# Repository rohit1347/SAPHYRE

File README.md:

# SAPHYRE
PCB for final year project.

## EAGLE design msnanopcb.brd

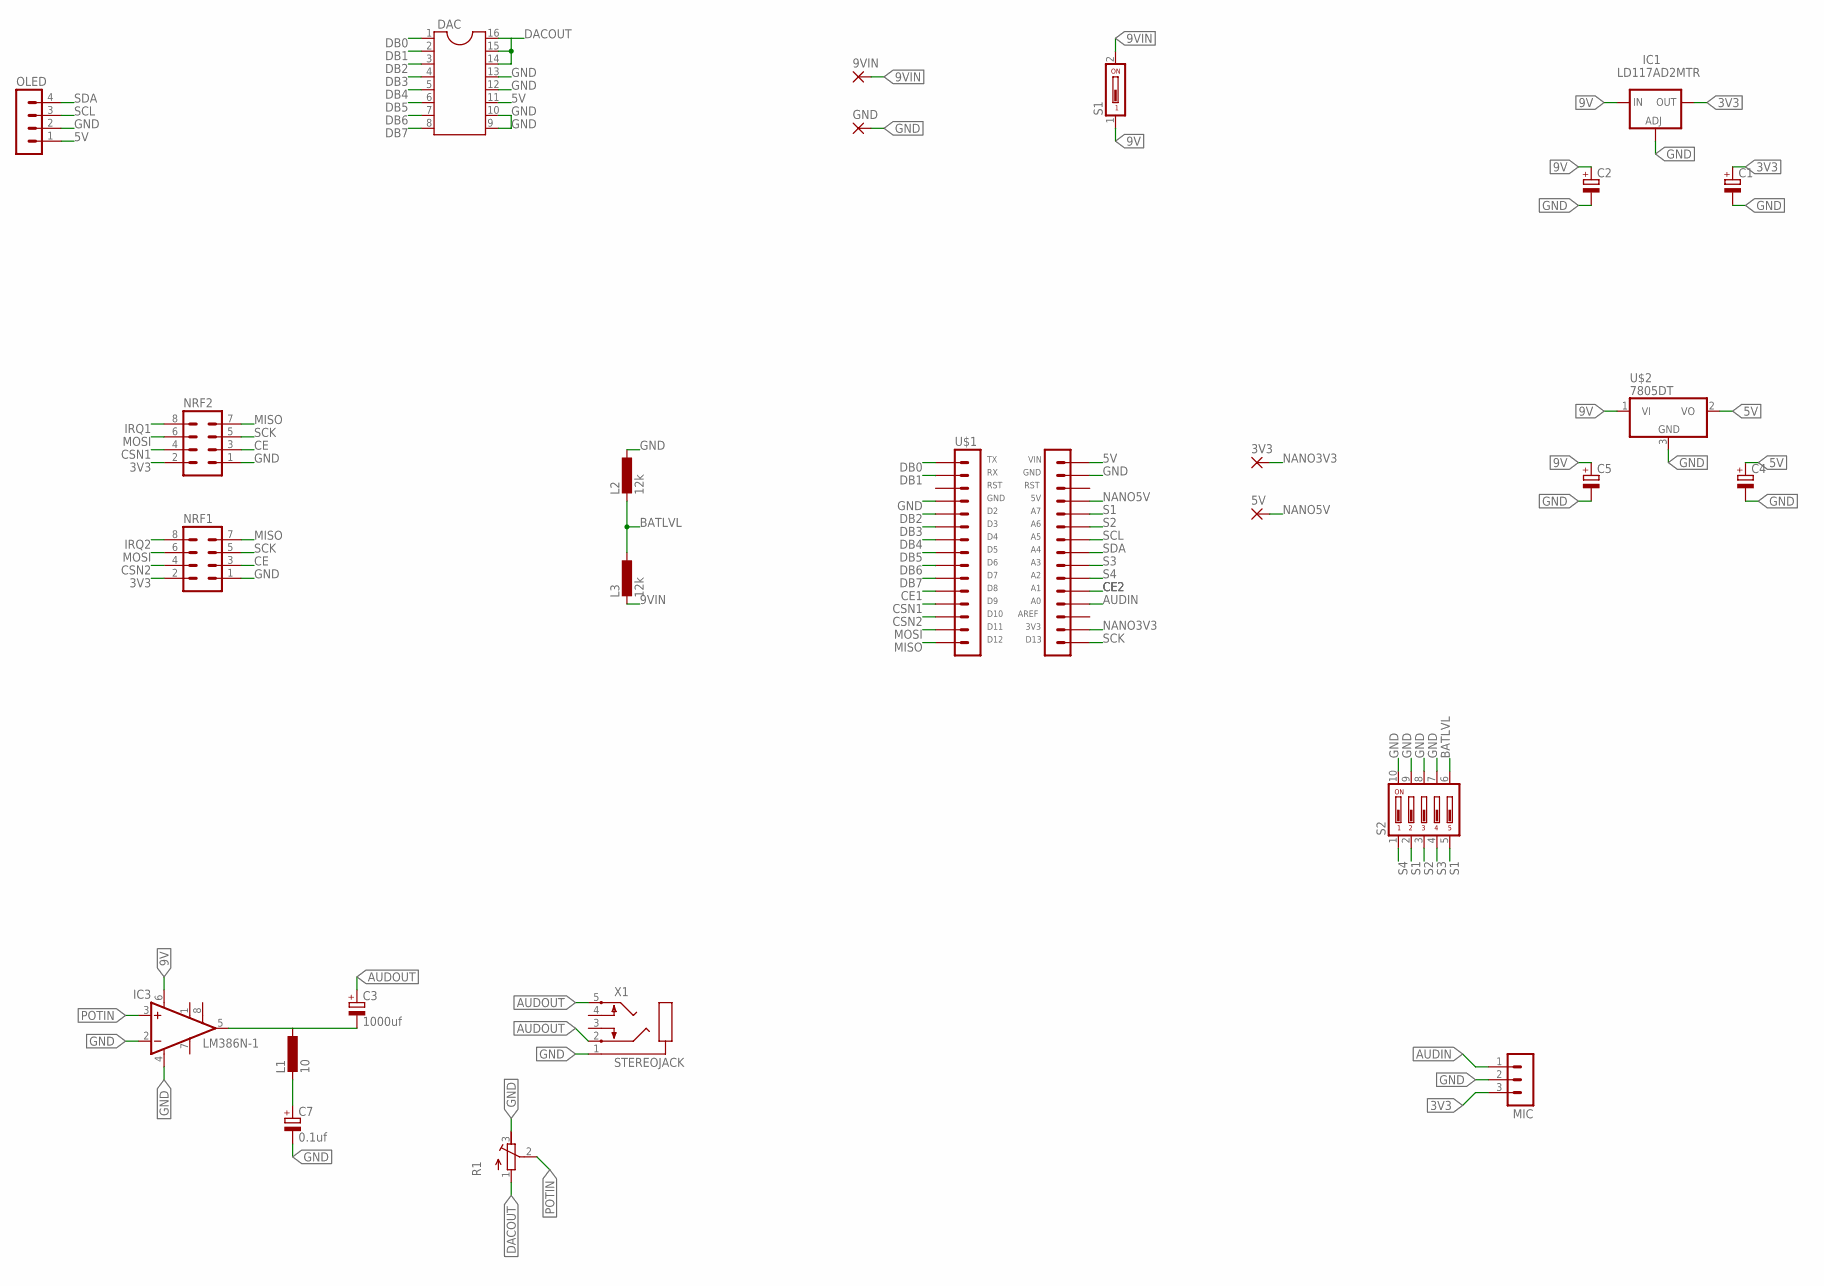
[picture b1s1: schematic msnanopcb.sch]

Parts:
3V3, 5V, 9VIN: WIREPADSMD1,27-254; SMD1,27-2,54
C1, C2, C4, C5: CPOL-EUE2,5-6E; E2,5-6E
C3: 1000uf; E3,5-8
C7: 0.1uf; E2-5
DAC: DIL16S; SOCKET-16
GND: WIREPADSMD1,27-254; SMD1,27-2,54
IC1: LD117AD2MTR; D2PACK
IC3: LM386N-1; DIL08
L1: 10; 0204/7
L2, L3: 12k; 0204/7
MIC: MA03-1
NRF1, NRF2: MA04-2
OLED: MA04-1
R1: R-TRIMM3296P; RTRIM3296P
S1: DS01; DS-01
S2: DS05; DS-05
U$1: ARD-NANO
U$2: 7805DT; TO252
X1: STEREOJACK; STX3100

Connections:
3V3: C1.+, IC1.2 (OUT), MIC.3, NRF1.2, NRF2.2
5V: C4.+, DAC.11, OLED.1, U$1.VIN, U$2.2 (VO)
9V: C2.+, C5.+, IC1.3 (IN), IC3.6 (VS), S1.1, U$2.1 (VI)
9VIN: 9VIN.1, L3.2, S1.2
AUDIN: MIC.1, U$1.A0
AUDOUT: C3.+, X1.2, X1.5
BATLVL: L2.2, L3.1, S2.6
CE: NRF1.3, NRF2.3
CE1: U$1.D8
CE2: U$1.A1
CSN1: NRF2.4, U$1.D9
CSN2: NRF1.4, U$1.D10
DACOUT: DAC.14, DAC.15, DAC.16, R1.1 (A)
DB0: DAC.1, U$1.TX
DB1: DAC.2, U$1.RX
DB2: DAC.3, U$1.D2
DB3: DAC.4, U$1.D3
DB4: DAC.5, U$1.D4
DB5: DAC.6, U$1.D5
DB6: DAC.7, U$1.D6
DB7: DAC.8, U$1.D7
GND: C1.-, C2.-, C4.-, C5.-, C7.-, DAC.9, DAC.10, DAC.12, DAC.13, GND.1, IC1.1 (ADJ), IC3.2 (-IN), IC3.4 (GND), L2.1, MIC.2, NRF1.1, NRF2.1, OLED.2, R1.3 (E), S2.7, S2.8, S2.9, S2.10, U$1.GND1, U$1.GND2, U$2.3 (GND), X1.1
IRQ1: NRF2.8
IRQ2: NRF1.8
MISO: NRF1.7, NRF2.7, U$1.D12
MOSI: NRF1.6, NRF2.6, U$1.D11
unnamed: C3.-, IC3.5 (OUT), L1.1
unnamed: C7.+, L1.2
NANO3V3: 3V3.1, U$1.3V3
NANO5V: 5V.1, U$1.5V
POTIN: IC3.3 (+IN), R1.2 (S)
S1: S2.2, S2.5, U$1.A7
S2: S2.3, U$1.A6
S3: S2.4, U$1.A3
S4: S2.1, U$1.A2
SCK: NRF1.5, NRF2.5, U$1.D13
SCL: OLED.3, U$1.A5
SDA: OLED.4, U$1.A4

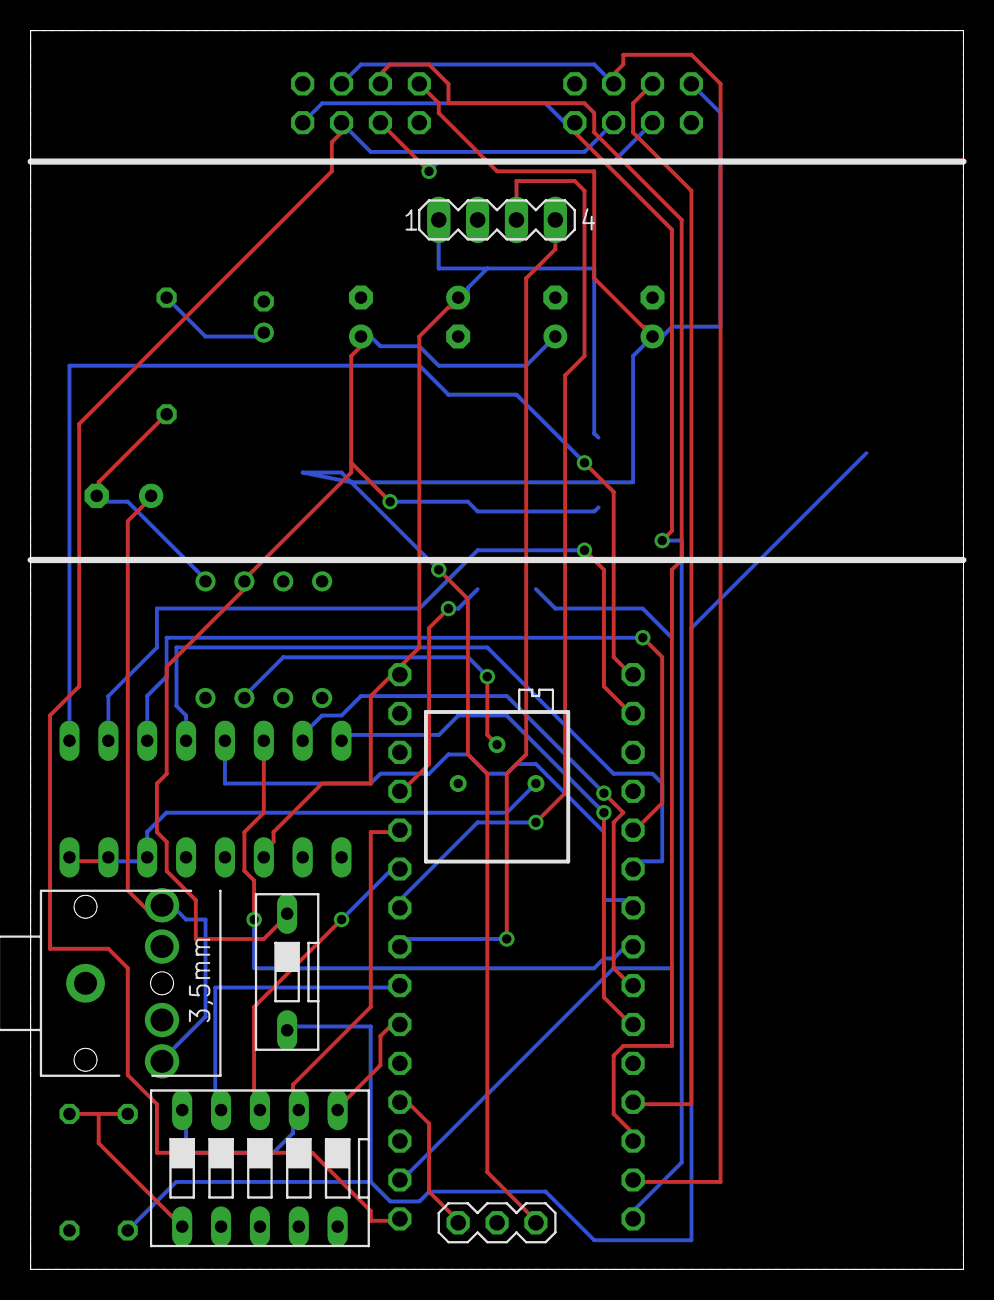
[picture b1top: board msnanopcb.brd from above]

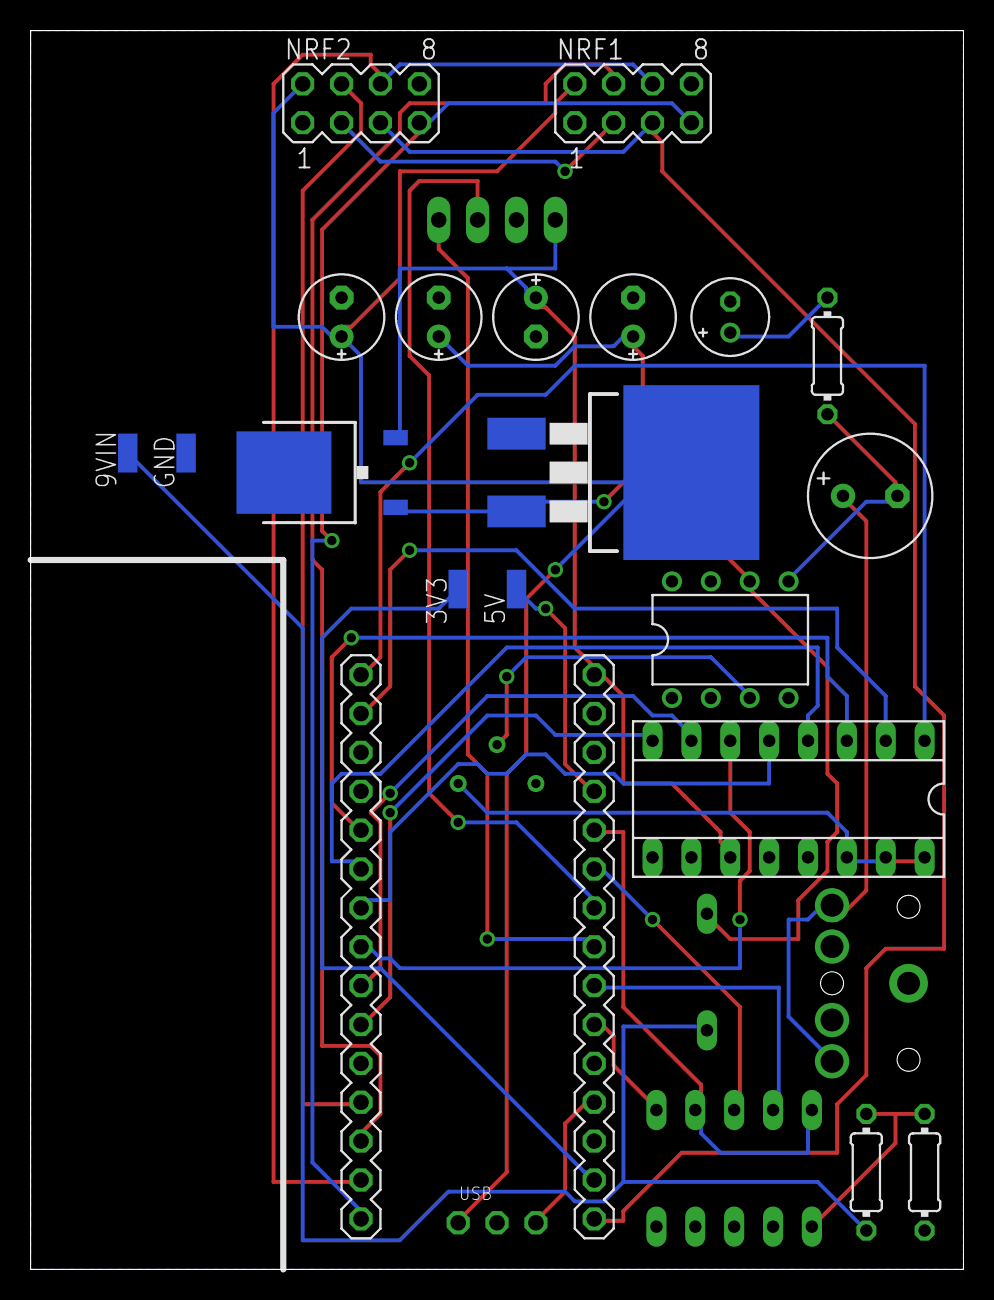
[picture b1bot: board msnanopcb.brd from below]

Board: 2 copper layers, 61.0 x 80.9 mm, 26 parts (20 on the bottom side), 34 nets.

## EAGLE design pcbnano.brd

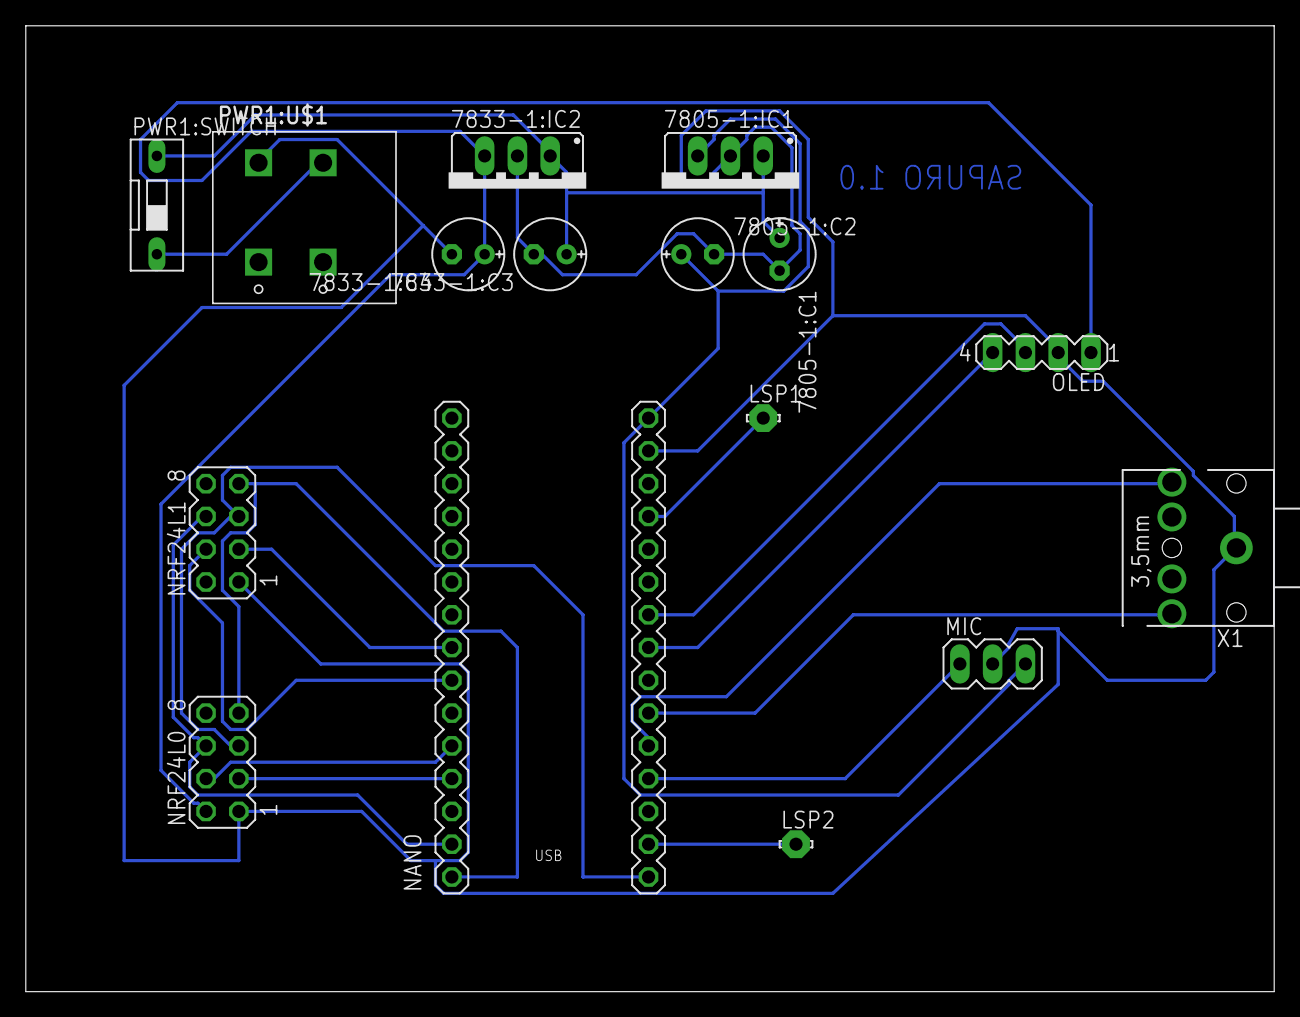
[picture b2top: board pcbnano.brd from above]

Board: 2 copper layers, 96.7 x 74.9 mm, 16 parts (0 on the bottom side), 19 nets.

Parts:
7805-1:C1, 7805-1:C2, 7833-1:C3, 7833-1:C4: E2,5-6E
7805-1:IC1, 7833-1:IC2: 78XXS
LSP1, LSP2: LSP10
MIC: MA03-1
NANO: ARD-NANO
NRF24L0, NRF24L1: MA04-2
OLED: MA04-1
PWR1:SWITCH: DS-01
PWR1:U$1: SPTBB2-A2; SPTB
X1: STEREOJACK; STX3100

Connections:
3V3NANO: LSP2.MP, NANO.3V3
5VNANO: LSP1.MP, NANO.5V
ALEFT: NANO.A2, X1.2
ARIGHT: NANO.A1, X1.5
AUDIO: MIC.1, NANO.A0
CE1: NANO.D9, NRF24L0.3
CE2: NANO.D5, NRF24L1.3
CSN1: NANO.D8, NRF24L0.4
CSN2: NANO.D6, NRF24L1.4
GND: 7805-1:C1.-, 7805-1:C2.-, 7805-1:IC1.GND, 7833-1:C3.-, 7833-1:C4.-, 7833-1:IC2.GND, MIC.2, NANO.GND2, NRF24L0.1, NRF24L1.1, OLED.2, PWR1:U$1.A2, X1.1
MISO: NANO.D12, NRF24L0.7, NRF24L1.7
MOSI: NANO.D11, NRF24L0.6, NRF24L1.6
PWR1:VCC9O: PWR1:SWITCH.1, PWR1:U$1.B2
SCK: NANO.D13, NRF24L0.5, NRF24L1.5
SCL: NANO.A5, OLED.3
SDA: NANO.A4, OLED.4
VCC5: 7805-1:C2.+, 7805-1:IC1.OUT, MIC.3, NANO.VIN
VCC9: 7805-1:C1.+, 7805-1:IC1.IN, 7833-1:C3.+, 7833-1:IC2.IN, PWR1:SWITCH.2
VCC33: 7833-1:C4.+, 7833-1:IC2.OUT, NRF24L0.2, NRF24L1.2, OLED.1

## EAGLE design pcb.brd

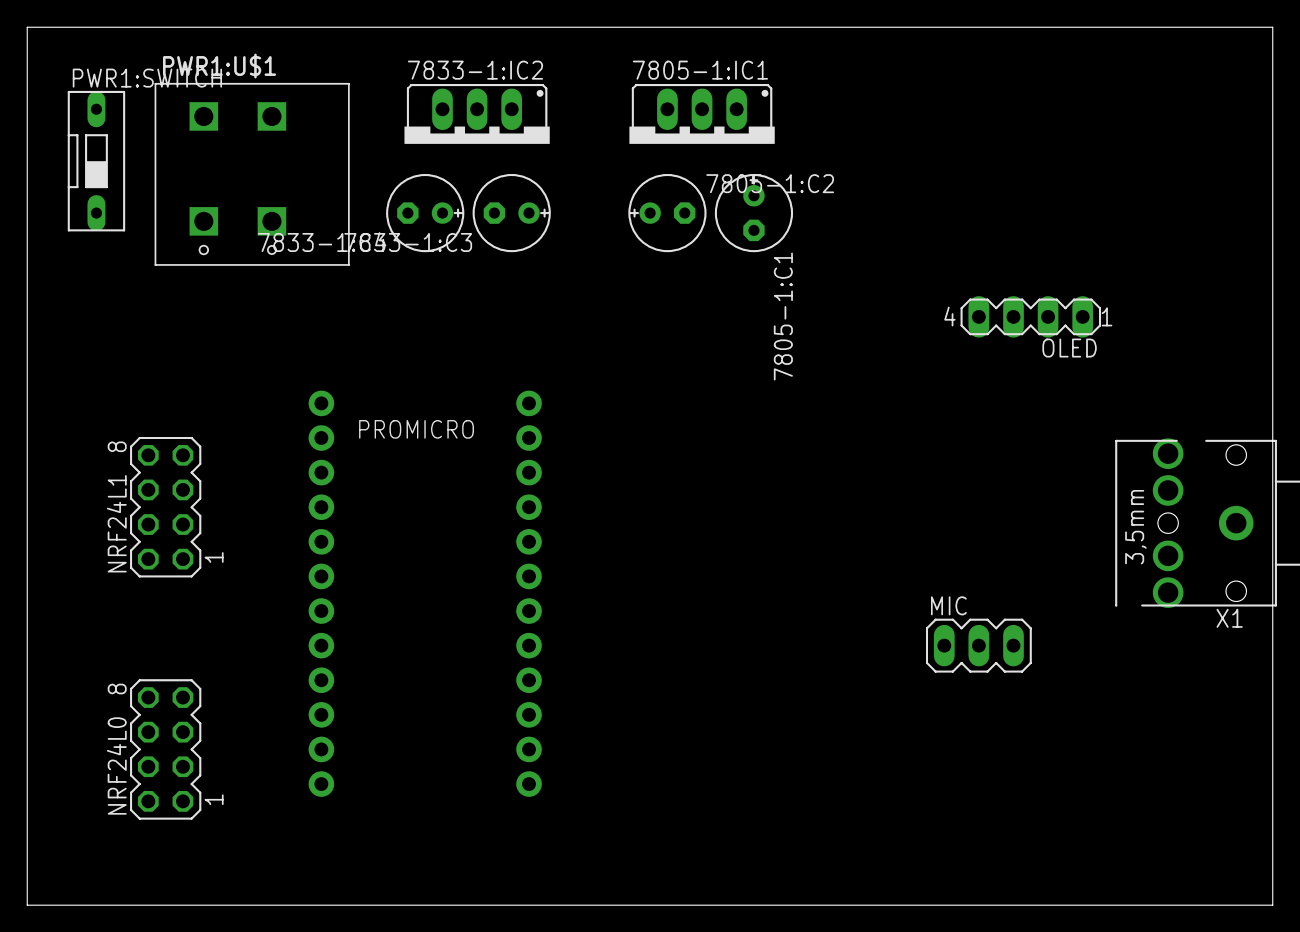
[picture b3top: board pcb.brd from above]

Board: 2 copper layers, 91.4 x 64.4 mm, 14 parts (0 on the bottom side), 17 nets, no tracks yet.

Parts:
7805-1:C1, 7805-1:C2, 7833-1:C3, 7833-1:C4: E2,5-6E
7805-1:IC1, 7833-1:IC2: 78XXS
MIC: MA03-1
NRF24L0, NRF24L1: MA04-2
OLED: MA04-1
PROMICRO: ARDUINO_PRO_MICRO
PWR1:SWITCH: DS-01
PWR1:U$1: SPTBB2-A2; SPTB
X1: STEREOJACK; STX3100

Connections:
ALEFT: PROMICRO.12, X1.2
ARIGHT: PROMICRO.13, X1.5
AUDIO: MIC.1, PROMICRO.17
CE1: NRF24L0.3, PROMICRO.11
CE2: NRF24L1.3, PROMICRO.9
CSN1: NRF24L0.4, PROMICRO.10
CSN2: NRF24L1.4, PROMICRO.8
GND: 7805-1:C1.-, 7805-1:C2.-, 7805-1:IC1.GND, 7833-1:C3.-, 7833-1:C4.-, 7833-1:IC2.GND, MIC.2, NRF24L0.1, NRF24L1.1, OLED.2, PROMICRO.4, PWR1:U$1.A2, X1.1
MISO: NRF24L0.7, NRF24L1.7, PROMICRO.15
MOSI: NRF24L0.6, NRF24L1.6, PROMICRO.14
PWR1:VCC9O: PWR1:SWITCH.1, PWR1:U$1.B2
SCK: NRF24L0.5, NRF24L1.5, PROMICRO.16
SCL: OLED.3, PROMICRO.6
SDA: OLED.4, PROMICRO.5
VCC5: 7805-1:C2.+, 7805-1:IC1.OUT, MIC.3, PROMICRO.21
VCC9: 7805-1:C1.+, 7805-1:IC1.IN, 7833-1:C3.+, 7833-1:IC2.IN, PWR1:SWITCH.2
VCC33: 7833-1:C4.+, 7833-1:IC2.OUT, NRF24L0.2, NRF24L1.2, OLED.1

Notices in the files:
parts and their libraries:
SparkFun-Boards: Licensing: Creative Commons ShareAlike 4.0 International - https://creativecommons.org/licenses/by-sa/4.0
